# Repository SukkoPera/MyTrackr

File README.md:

# MyTrackr
Arduino-Based GPS tracker

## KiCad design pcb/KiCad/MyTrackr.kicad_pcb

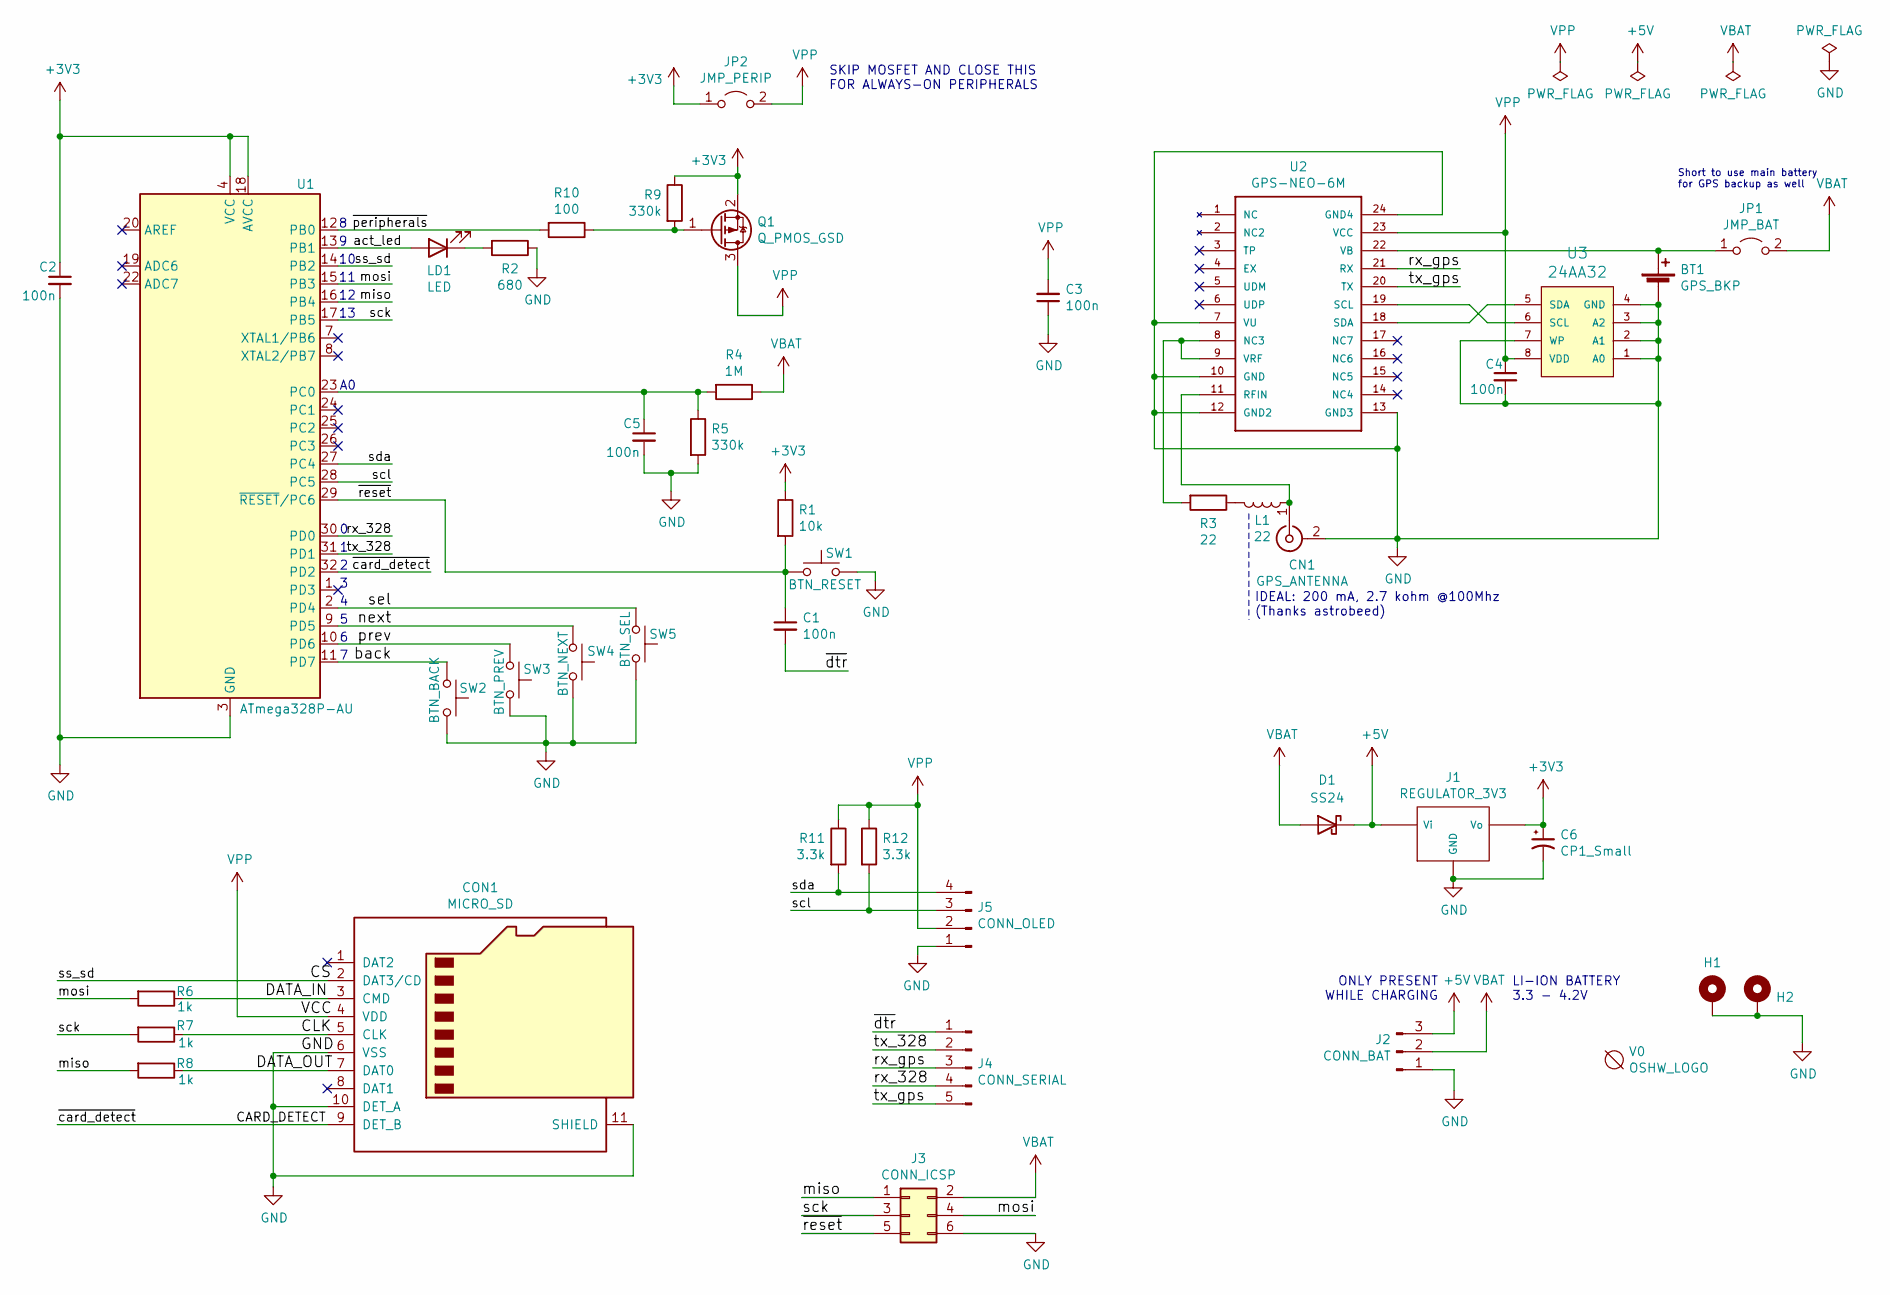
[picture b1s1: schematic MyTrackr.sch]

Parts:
BT1: GPS_BKP; BR1225A_KEYSTONE_1056
C1, C2, C3, C4, C5: 100n; C_0805_2012Metric_Pad1.18x1.45mm_HandSolder
C6: CP1_Small; CP_EIA-7343-30_AVX-N_Pad2.25x2.55mm_HandSolder
CN1: GPS_ANTENNA; CONN-RF-UFL
CON1: MICRO_SD; GCT-MEM2055-00-190-01-A
D1: SS24; D_SMA
H1, H2: MountingHole_Pad; Screw_Hole_Plated_3mm
J1: REGULATOR_3V3; PinHeader_1x03_P2.54mm_Vertical
J2: CONN_BAT; PinHeader_1x03_P2.54mm_Vertical
J3: CONN_ICSP; PinHeader_2x03_P2.54mm_Vertical
J4: CONN_SERIAL; PinHeader_1x05_P2.54mm_Vertical
J5: CONN_OLED; PinHeader_1x04_P2.54mm_Vertical
JP1: JMP_BAT; SolderJumper-2_P1.3mm_Open_TrianglePad1.0x1.5mm
JP2: JMP_PERIP; SolderJumper-2_P1.3mm_Open_TrianglePad1.0x1.5mm
L1: 22; R_0805_2012Metric_Pad1.20x1.40mm_HandSolder
LD1: LED; LED_0805_2012Metric_Pad1.15x1.40mm_HandSolder
Q1: Q_PMOS_GSD; SOT-23
R1: 10k; R_0805_2012Metric_Pad1.20x1.40mm_HandSolder
R2: 680; R_0805_2012Metric_Pad1.20x1.40mm_HandSolder
R3: 22; R_0805_2012Metric_Pad1.20x1.40mm_HandSolder
R4: 1M; R_0805_2012Metric_Pad1.20x1.40mm_HandSolder
R5, R9: 330k; R_0805_2012Metric_Pad1.20x1.40mm_HandSolder
R6, R7, R8: 1k; R_0805_2012Metric_Pad1.20x1.40mm_HandSolder
R10: 100; R_0805_2012Metric_Pad1.20x1.40mm_HandSolder
R11, R12: 3.3k; R_0805_2012Metric_Pad1.20x1.40mm_HandSolder
SW1: BTN_RESET; SingleButtonSmall
SW2: BTN_BACK; SW_SPST_EVPBF
SW3: BTN_PREV; SW_SPST_EVPBF
SW4: BTN_NEXT; SW_SPST_EVPBF
SW5: BTN_SEL; SW_SPST_EVPBF
U1: ATmega328P-AU; TQFP-32_7x7mm_P0.8mm
U2: GPS-NEO-6M; GPS24P-SMD-1.1-16X12.2MM
U3: 24AA32; tssop-8
V0: OSHW_LOGO; OSHW-Logo_5.7x6mm_Copper

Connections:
+3V3: C2.1, C6.1, J1.1 (Vo), JP2.1 (A), Q1.2 (S), R1.1, R9.1, U1.4 (VCC), U1.6 (VCC), U1.18 (AVCC)
+5V: D1.1 (K), J1.3 (Vi), J2.3
/CARD_DETECT: CON1.9 (DET_B), U1.32 (PD2)
/CLK: CON1.5 (CLK), R7.1
/CS: CON1.2 (DAT3/CD), U1.14 (PB2)
/DATA_IN: CON1.3 (CMD), R6.1
/DATA_OUT: CON1.7 (DAT0), R8.1
/act_led: LD1.2 (A), U1.13 (PB1)
/back: SW2.1, U1.11 (PD7)
/miso: J3.1, R8.2, U1.16 (PB4)
/mosi: J3.4, R6.2, U1.15 (PB3)
/next: SW4.1, U1.9 (PD5)
/prev: SW3.1, U1.10 (PD6)
/rx_328: J4.4, U1.30 (PD0)
/rx_gps: J4.3, U2.21 (RX)
/sck: J3.3, R7.2, U1.17 (PB5)
/scl: J5.3, R12.2, U1.28 (PC5)
/sda: J5.4, R11.2, U1.27 (PC4)
/sel: SW5.1, U1.2 (PD4)
/tx_328: J4.2, U1.31 (PD1)
/tx_gps: J4.5, U2.20 (TX)
/~dtr: C1.2, J4.1
/~peripherals: R10.2, U1.12 (PB0)
/~reset: C1.1, J3.5, R1.2, SW1.1, U1.29 (~RESET~/PC6)
GND: BT1.2 (-), C2.2, C3.1, C4.2, C5.2, C6.2, CN1.2 (Ext), CON1.6 (VSS), CON1.10 (DET_A), CON1.11 (SHIELD), H1.1, H2.1, J1.2 (GND), J2.1, J3.6, J5.1, R2.1, R5.2, SW1.2, SW2.2, SW3.2, SW4.2, SW5.2, U1.3 (GND), U1.5 (GND), U1.21 (GND), U2.7 (VU), U2.10 (GND), U2.12 (GND2), U2.13 (GND3), U2.24 (GND4), U3.1 (A0), U3.2 (A1), U3.3 (A2), U3.4 (GND), U3.7 (WP)
unnamed: BT1.1 (+), JP1.1 (A), U2.22 (VB)
unnamed: C5.1, R4.2, R5.1, U1.23 (PC0)
unnamed: CN1.1 (In), L1.1, U2.11 (RFIN)
unnamed: L1.2, R3.1
unnamed: LD1.1 (K), R2.2
unnamed: Q1.1 (G), R9.2, R10.1
unnamed: R3.2, U2.8 (NC3), U2.9 (VRF)
unnamed: U2.18 (SDA), U3.5 (SDA)
unnamed: U2.19 (SCL), U3.6 (SCL)
VBAT: D1.2 (A), J2.2, J3.2, JP1.2 (B), R4.1
VPP: C3.2, C4.1, CON1.4 (VDD), J5.2, JP2.2 (B), Q1.3 (D), R11.1, R12.1, U2.23 (VCC), U3.8 (VDD)

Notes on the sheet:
Short to use main battery for GPS backup as well
IDEAL: 200 mA, 2.7 kohm @100Mhz (Thanks astrobeed)
SKIP MOSFET AND CLOSE THIS FOR ALWAYS-ON PERIPHERALS
LI-ION BATTERY 3.3 - 4.2V
ONLY PRESENT WHILE CHARGING

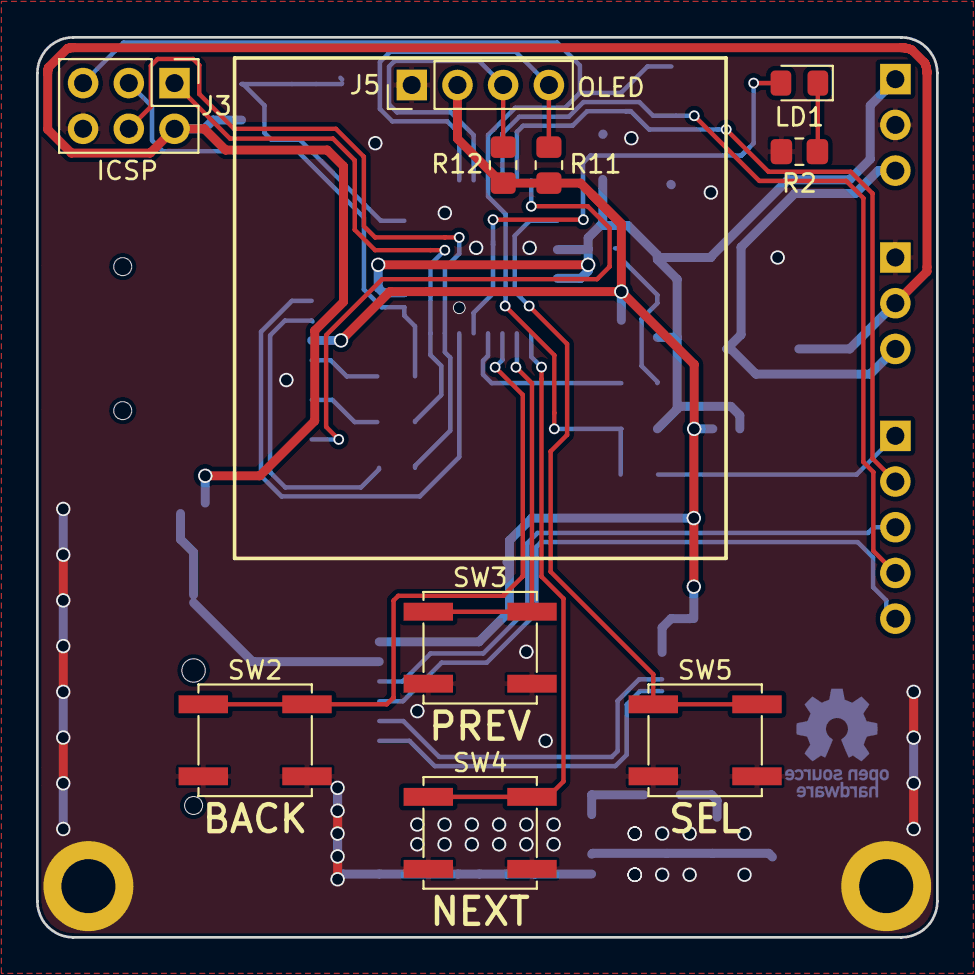
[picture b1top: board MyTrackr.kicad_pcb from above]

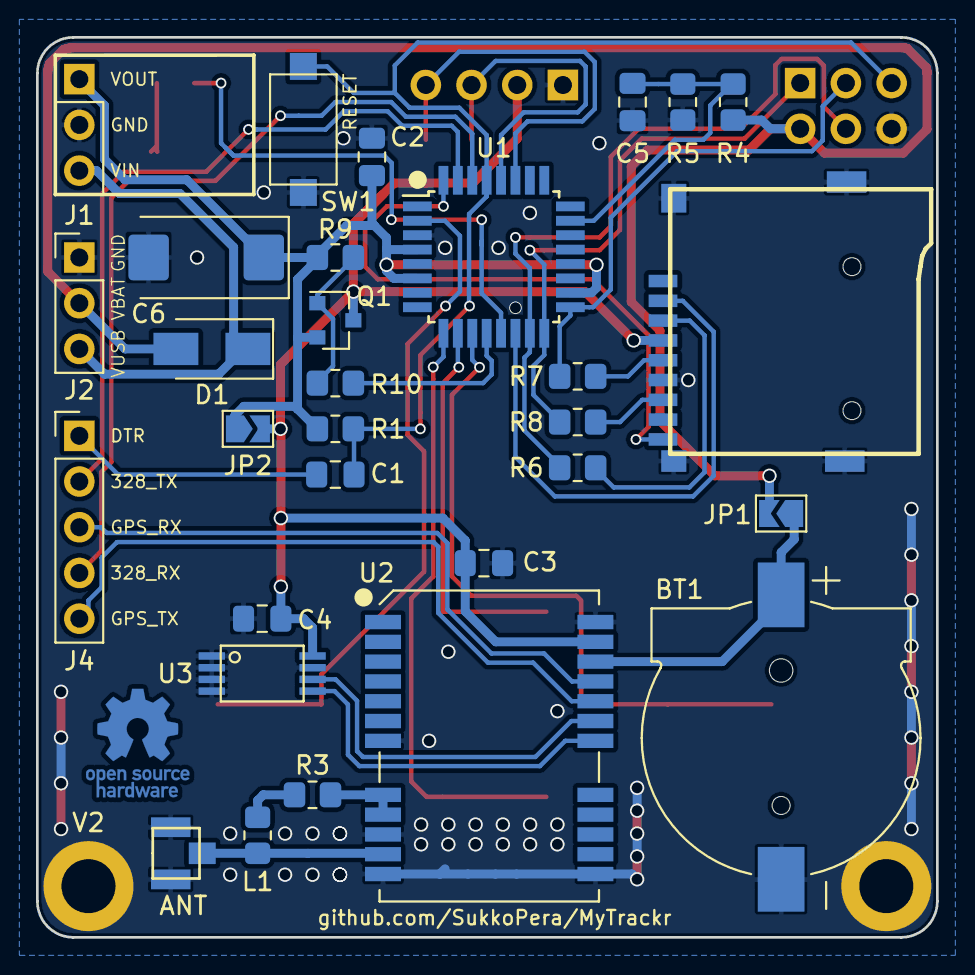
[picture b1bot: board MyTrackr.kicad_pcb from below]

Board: 2 copper layers, 50.0 x 50.0 mm, 43 parts (31 on the bottom side), 36 nets.

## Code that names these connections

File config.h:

#ifndef CONFIG_H_INCLUDED
#define CONFIG_H_INCLUDED

/* Define to actually enable SD support through the SdFatLib library. If both
 * this and ENABLE_SD_FAT16 are not defined, logging will be redirected to the
 * serial monitor, useful fo debugging.
 */
//~ #define ENABLE_SD_FATLIB

/* Define this to enable SD support through the FAT16 library. This saves flash
 * space but has a number of restrictions, such as only supporting 8+3 filenames
 * and not supporting SDHC (i.e. > 2 GB) cards.
 *
 * Get the library at https://github.com/greiman/Fat16
 */
#define ENABLE_SD_FAT16

// SD Slave-Select (SS, also known as CS) pin
#define SD_CHIPSELECT 10

// Time a fix is considered valid (sec)
#define DATA_VALID_TIME 10

/* Number of decimal digits to use when logging latitude and longitude.
 *
 * 6 digits allows for precision up to 4 inches. See here for details:
 * http://lightmanufacturingsystems.com/heliostats/support/decimal-latitude-longitude-accuracy/
 */
#define LATLON_PREC 6

// Use signed latitude/longitude instead of N/S and E/W
//~ #define USE_SIGNED_LATLON

// Default logging interval (sec)
#define DEFAULT_LOG_INTERVAL 10

/* Define to enable log distance menu
 */
#define ENABLE_DISTANCE_MENU

/* Default logging distance: position will not be logged unless it is at least
 * this far from the previously logged position (meters, 0 = disabled)
 */
#define DEFAULT_LOG_DISTANCE 0

/* Define to enable log rotation menu
 */
#define ENABLE_ROTATION_MENU

/* Default log rotation interval
 */
#define DEFAULT_LOG_ROTATION LOGROT_DAILY

/* Define to enable the screen backlight timeout menu
 */
#define ENABLE_BACKLIGHT_MENU

/* Default screen backlight timeout: time interval from last keypress to turn
 * screen off (s)
 */
#define DEFAULT_BACKLIGHT_TIMEOUT 30

/* Default offset hours from gps time (UTC).
 * Ideally, it should be possible to learn the time zone based on the GPS
 * position data.  However, that would require a complex library, probably
 * incorporating some sort of database using Eric Muller's time zone shape maps,
 * at http://efele.net/maps/tz/
 *
 * We default to Central European Time (GMT+1).
 */
#define DEFAULT_TZ_OFFSET 1

/* Number of lines on screen to use for the menu. Font-size dependent
 */
#define MENU_LINES 5

/* Pins keys are connected to. NEXT and SELECT are required, BACK and PREV can
 * be left undefined.
 *
 * Note that by default these are on PD4-7, corresponding to PCINT20-23.
 */
#define KEY_BACK_PIN 7
#define KEY_PREV_PIN 6
#define KEY_NEXT_PIN 5
#define KEY_SELECT_PIN 4

#define ENABLE_SOFT_POWEROFF
#define KEY_INT_VECT PCINT2_vect
#define KEY_PCICR_BIT PCIE2
#define KEY_PCMSK_REG PCMSK2
#ifdef KEY_BACK_PIN
#define PCMSK_BIT_BACK (1 << PCINT20)
#else
#define PCMSK_BIT_BACK 0
#endif
#ifdef KEY_PREV_PIN
#define PCMSK_BIT_PREV (1 << PCINT21)
#else
#define PCMSK_BIT_PREV 0
#endif
#define KEY_PCMSK_BITS (PCMSK_BIT_BACK | PCMSK_BIT_PREV | (1 << PCINT22) | (1 << PCINT23))

// Time interval that SELECT+NEXT must be held to toggle keylock (ms)
#define KEY_LOCK_DELAY 2000

// "Alive led": pin led is connected to
#define ALIVE_LED_PIN 9

// "Alive led": blink for 75 ms every 10 s
#define ALIVE_LED_ON_TIME 75
#define ALIVE_LED_OFF_TIME 10000UL

// Pin that controls SD/GPS/Screen power (through a MOSFET, of course)
#define PERIPHERALS_POWER_PIN 8

// Analog pin used to measure battery level
#define BATTERY_PIN A0

/* Number of times to sample the battery for each measure (up to 255) and delay
 * between measures (ms).
 */
#define BATTERY_ITERATIONS 10
#define BATTERY_IT_DELAY 20

// Battery measurement interval (s)
#define BATTERY_INTERVAL 60

// Number of ADC steps
#define BATTERY_STEPS 1024

// Percentage at which battery is marked "low"
#define BATTERY_LOW_PERC 20

// Percentage at which battery is marked "critically low"
#define BATTERY_CRITLOW_PERC 5

/* When battery is critically low, the device will be turned off after this
 * number of seconds has passed.
 */
#define CRITLOW_CUTOFF_TIME 10

/* Battery level is measured against the internal 1.1v reference, but such
 * reference can be up to 10% off. If you want measurements to be more accurate,
 * measure the AREF pin for your particular chip and insert its value here (mV).
 */
#define REAL_1_1_REF 1100

/* Since the raw battery voltage is greater than 1.1v, a voltage divider is
 * needed to bring the level to one that can be measured. We recommend using a
 * 1M + 330K resistor combination. If you want measurements to be more accurate,
 * measure your resistors with a multimeter and put the exact values here.
 *
 * Note that R1 must always be the bigger resistor.
 */
#define BATTERY_R1 1018000UL
#define BATTERY_R2 331000UL

/* Battery voltage points used to indicate remaining battery charge. These can
 * be fine-tuned as described on the wiki.
 *
 * The default values are fine with my 18650's.
 */
const byte BATTERY_POINTS_NO = 5;
//~ const unsigned int BATTERY_POINT_OFFSET = 150;
//~ const byte BATTERY_POINTS[BATTERY_POINTS_NO] PROGMEM = {222, 204, 191, 185, 166};

// 605050 2000 mAh
const unsigned int BATTERY_POINT_OFFSET = 160;
const byte BATTERY_POINTS[BATTERY_POINTS_NO] PROGMEM = {248, 233, 227, 220, 211};

/* DEFINE this to DISABLE debug messages
 */
#define NDEBUG

#endif

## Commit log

2016-06-09 Add gpssim
2016-06-09 Add .gitignore
2016-06-09 Free some RAM
2016-06-12 First testable release!
2016-06-12 Handle altitude validity
2016-06-12 Blink sat & SD icon for relevant failures
2016-06-13 Fix altitude & some source reorganization
2016-06-14 Log HDOP as well
2016-06-16 Only include SD library if needed
2016-06-16 This version uses the AdaFruit OLED lib instead of u8glib for driving the OLED display. I was told it uses less resources, but it actually looks the opposite to me, so this is going to sit on this br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
2016-06-16 Add config menu. Lots of things to hone...
2016-06-16 Do not exceed screen height in menus
2016-06-16 Formatting fixes
2016-06-16 Allow setting DST and TZ offset from menu
2016-06-16 Allow starting/stopping logging from menu
2016-06-16 Fix trailing CR in log header with SD disabled
2016-06-19 Put menu strings in flash, to save RAM
2016-06-19 Move MenuHandler to a separate file
2016-06-19 Fix spacing
2016-06-19 Use different syntax
2016-06-19 Save more RAM
2016-06-19 Enable SD by default
2016-06-19 Remove cruft
2016-06-19 Save even more RAM
2016-06-19 Allow setting log frequency from menu
2016-06-19 Save 2 bytes of flash
2016-06-19 Always redraw menu and improve MenuHandler interface. Note that menu must always be redrawn since header is always updated at the moment.
2016-06-19 Simplify key handling. Also support a PREV button, if available.
2016-06-19 Save flash
2016-06-19 Show logging status in header bar
2016-06-24 Respect minimum logging distance
2016-06-24 Disable logging by default
2016-06-24 Support both SdFatLib and Fat16. At the moment neither is working tho :(.
2016-06-25 Support both SdFatLib and Fat16. At least the latter is working fine now.
2016-06-25 Save some flash/RAM and add some meaningful default values
2016-06-25 Only consider fix valid if number of sats > 0
2016-06-26 Point is good if distance is == minimum
2016-06-26 Use 7 digits precision
2016-07-10 Fix DST detection
2016-07-10 Make log rotation menu optional. Still not implemented anyway...
2016-07-10 Measure and display battery level
2016-10-09 Turn screen off to save power
2016-10-09 Sim starts slower
2016-10-09 Use /dev/ttyUSB
2016-10-09 Revamp battery charge handling Work in progress...
2016-10-09 Remove useless battery logs
2016-10-09 Fix typo
2016-10-09 Correct CSV labels
2016-11-02 Use explicit speed units for gpsbabel understanding
2017-05-07 Add "Alive LED"
2017-05-07 Display Altitude
2017-05-07 Use LATLON_PREC everywhere
2017-05-07 Only use 6 decimal digits
2017-05-07 Port to u8g2 This was not so good an idea, since it needs many more resources:
    Before:
    Lo sketch usa 25828 byte (80%) dello spazio disponibile per i programmi. Il massimo è 32256 byte.
    Le variabili globali usano 1645 byte (80%) di memoria dinamica, lasciando altri 403 byte liberi per le variabili locali. Il massimo è 2048 byte.
    After:
    Lo sketch usa 27162 byte (84%) dello spazio disponibile per i programmi. Il massimo è 32256 byte.
    Le variabili globali usano 1999 byte (97%) di memoria dinamica, lasciando altri 49 byte liberi per le variabili locali. Il massimo è 2048 byte.
2017-05-07 Turn screen off after 30 seconds
2017-05-07 Show selected entry in menus
2017-05-07 Reset current menu item when menu is opened
2017-05-07 Use pgm_read_ptr() where applicable
2017-05-08 Tidy some things up
2017-05-08 Implement Log Rotation
2017-05-08 Implement $GPGLL and fix checksum calculation
2017-05-08 Compile fix for when both ENABLE_SD_FATLIB and ENABLE_SD_FAT16 are disabled
2017-05-09 Tidy up a bit
2017-05-09 Make log distance menu optional
2017-05-09 Add DATA_VALID_TIME constant
2017-05-09 Save options to EEPROM
2017-05-09 Save some SRAM/flash
2017-05-09 Fix indentation
2017-05-09 Save more SRAM/flash
2017-05-10 Remove misleading comment
2017-05-13 Implement key repeat and keylock
2017-05-13 Add/Update icons
2017-05-17 Add first version of PCB
2017-05-17 Rotate page and minor fixes
2017-05-17 Rename ;)
2017-05-17 Add voltage divider for battery
2017-05-17 Remove ECR markers
2017-05-17 Remove ECR markers (Really!)
2017-05-18 Add resistors on SPI lines, add cap on A0, add pull-down on MOSFET
2017-05-29 Replace DIP 328 with TQFP
2017-06-11 Update schematics
2017-06-11 Fix MOSFET orientation, add resistor on gate and change pull-up value
2017-08-03 Add prototype PCB design files
2017-09-06 Corrections and tweaks after first prototype
2017-09-06 Expand zones
2017-09-08 Add screw holes, smooth corners and more
2017-09-08 Add screw hole footprint
2017-09-10 Add board package
2018-03-26 Fix platform/board names
2018-03-26 Fix key pins according to PCB
2018-03-26 Use standard value of REAL_1_1_REF by default
2018-03-26 Implement soft power off
2018-03-26 Initialize pins for back/prev keys properly
2018-03-26 Add u8g.begin() just in case
2018-03-26 Remove trailing empty line
2018-03-26 Add empty line
2018-03-26 Make screen backlight timeout configurable from menu
2018-03-26 Fix log message
2018-03-26 Use shorter labels
2018-03-26 Make 15 seconds... 15
2018-03-26 Update for latest changes in AABlink API
2018-03-26 Use led to communicate status 1 blink = Got position, battery OK 2 blinks = No position, battery OK 3 blinks = Battery low
2018-03-27 Use custom font and show arrows in menus Use reduced charset to save flash
2018-03-27 Implement Back button in menus
2018-03-27 Add forgotten file :(
2018-03-27 Fix .gitignore
2018-03-27 Use "check" symbol for selected item in menus
2018-04-20 Add playground ;)
2018-08-26 Put all information on a single screen
2018-08-26 Don't turn on/Auto turn off on critically low battery
2021-01-10 Move project to KiCad 5.1.9, make all libs/footprints local
2021-01-10 Remove old cruft
2021-01-12 Connect all grounds, use meaningful signal names
2021-01-12 Use KiCad's 328 symbol and add MOSFET-bypass jumper
2021-01-12 Make custom footprint for reset button
2021-01-14 Add i2c pull-ups
2021-02-21 Minor fixes after PCB production
